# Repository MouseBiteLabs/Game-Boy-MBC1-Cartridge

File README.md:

# Game Boy MBC1 Cartridge

This is my design of a flashable MBC1-based cartridge for the Game Boy. The MBC1 mapper was used in many of the earlier Game Boy games, such as the Super Mario Land series, the Donkey Kong Land series, Metroid II, and one of my personal favorites - the original Link's Awakening. 

This circuit board should cover most, if not all, MBC1 games. The features are as follows:

- Able to make games that use 512 KB (4 Mbit) of ROM and 256 Kbit of RAM, or 2 MB (16 Mbit) of ROM and 64 Kbit of RAM
- Compatibility with all four of the major Game Boy battery management ICs - MM1026, MM1134, BA6129, and BA6735
- The option to add battery backup to the cartridge *without* the need of the original battery management ICs - perfect for MBC1 donors that didn't have batteries in them
- Lower battery consumption compared to some of the original cartridges
- Fully compatible with the <a href="https://www.gbxcart.com/">GBxCart RW</a> so you can transfer games and save files to and from the board

All gerbers and source files can be found in this repo, as this project is fully open source. Technical documentation of the board can be found in the Technical folder.

## Important Things Before You Start

1) To use this board, you need to have an original Game Boy game that uses an MBC1 mapper chip. <a href="https://catskull.net/gb-rom-database/">You can find a list of games and their mappers here</a>. Use the search function. Please note the RAM is in bytes, not bits. Since SRAM in this repo is defined in bits, you need to convert by multiplying the number of bytes by 8.
2) You will need to remove the MBC1 from your donor cartridge for use on this board. This will require a hot air rework station or a hot plate. There's a list below of other parts you can re-use from the donor cartridge.
3) When soldering parts on, it's a good idea to put kapton tape or otherwise cover the bottom cartridge edge. You do not want to get solder on the cartridge contacts.
4) I am not responsible for any damage you do to your self or your property. Attempt this project at your own risk.
5) I do not guarantee design compatibility. You may encounter issues with certain games. There is also a chance I have made an error in the design or the BOM - if this is the case, I will do everything I can to address the problem as quickly as possible.
6) If you are using this board to make games other than for personal use, you must have permission from the originator to use and distribute any ROM images or other related material. You are responsible for making sure you adhere to any license requirements.

DO NOT use my circuit boards for profiting from stolen work - this especially includes homebrew content, ROM hacks, and using fan-made labels without permission from the originator. **Support original creators!**

## Board Characteristics and Order Information

The zipped folder contains all the gerber files for this board. The following options **must** be chosen when ordering boards for yourself.

- Thickness: 0.8mm
- Surface Finish: ENIG
- Gold Fingers: Yes, 30° chamfer

**I sell this blank circuit board on Etsy, so you don't have to buy a bunch of multiples if you don't want to.** (Click the banner!)

You can alternatively use the zipped folder at any board fabricator you like. You may also buy the board from PCBWay using this link (disclosure: I receive 10% of the sale value to go towards future PCB orders of my own):

<a href="https://oshpark.com/shared_projects/bYJcF53Z">The board is also listed on OSH Park as well.</a> **Be sure to get them in 0.8mm thickness if you order from here.**

## Required Equipment

The EEPROMs on the board needs to be programmed somehow. I recommend using the GBxCart, as mentioned. These boards are fully compatible with it, and it makes reflashing games extremely easy using <a href="https://github.com/lesserkuma/FlashGBX">lesserkuma's FlashGBX software</a>.

Alternatively, you can buy an EEPROM programmer with a TSOP adapter. The downside to this method is that you have to desolder the chip every time you want to program it. The <a href="https://flashcatusb.com/">FlashcatUSB</a> is one popular option in retro spaces.

## Battery Safety

When assembling a board, I recommend populating all the parts *except* the battery, and getting it to run initially without it. This is to make it easier to fix any solder connections that might need fixing, without having to worry about getting the battery hot. And if you need to rework anything near the battery after you've put it on the board, be safe and remove it before putting a hot soldering iron next to it.

And this should go without saying, but if you're assembling these boards with a hot plate or hot air, *do not* solder the battery on this way. You should use an iron, and keep heat off of the battery as much as possible. 

(Also check polarity!)

## Board Configurations

The board comes with four sets of jumper pads for solder bridges. SJ1 and SJ2 require you to solder bridge the middle pad either to the top pad or the bottom pad. SJ3 and SJ4 are configured by either leaving them alone or bridging them with solder. Here are the situations where you need to add solder bridges.

### RAM Size Selection (SJ1 and SJ2, or SW1)

These two sets of pads are labelled "RAM SIZE" in the middle of the board. Soldering them will configure the max RAM *and* ROM size. You must configure these pads for every game you make - do not leave them empty (if you have no SRAM, solder to the "64K" setting to maximize ROM space). <a href="https://catskull.net/gb-rom-database/">You can find a list of games here with their respective ROM and RAM sizes.</a>

- Solder bridge SJ1 and SJ2 from their middle pads to the top pads for games that have larger ROM sizes (up to 2 MB, or 16 Mbit of ROM, and up to 64 Kbit of RAM).

- Solder bridge SJ1 and SJ2 from their middle pads to the bottom pads for games that have larger RAM sizes (up to 512 KB, or 4 Mbit of ROM, and up to 256 Kbit of RAM).

- SJ1 and SJ2 must be soldered in the same direction.

- The footprint of these selection pads should allow for a DPDT switch, part number CAS-220A1, to be placed on these pads instead of having to bridge the pads with solder.

### Using an MM1134 or BA6735 for U4 (SJ3)

Bridge the jumper SJ3 if you have either an MM1134 or BA6735 for U4, specifically. Any other battery management IC must leave SJ3 unsoldered.

### Making Games Without RAM (SJ4)

If your game does not have RAM on it (and therefore, you don't need the battery management IC U4), bridge SJ4 with solder. **Do not** bridge SJ4 if you are using U5 (TPS3613) instead of U4.

## Test Points and Final Checkout

On the back of the board are five test points. Here's where they are connected:

- TP1: SRAM supply voltage
- TP2: Battery voltage (after R1)
- TP3: Battery voltage (positive terminal of battery)
- TP4: Ground
- TP5: VCC input voltage

After you assemble your game, you should measure the current out of the battery. But first, you should program it with the GBxCart, or if you programmed the EEPROM separately, put it into a Game Boy and cycle power once. Then, flip the PCB upside down on a non-conductive surface (not your leg), and set your multimeter in DC millivolts (or volts). Put the positive probe on TP3 and the negative probe on TP2. If you used a 10kΩ for R1, as indicated in the BOM, you should read a voltage in the single of millivolts. If you have something much higher, especially voltages above 30mV, then you likely have an issue or short circuit on the board somewhere.

**Note: You need to power up the game at least once before battery currents will make sense - the battery management ICs can start up in an unknown state before applying main power to the board.**

To estimate battery life, see <a href="https://github.com/MouseBiteLabs/Game-Boy-MBC1-Cartridge/tree/main/Technical#estimating-battery-life">this section in the Technical Design Document</a>, or for more in-depth analysis, <a href="https://hackaday.io/project/11864-tritiled/log/72554-determining-maximum-runtime-176-to-202-years-cr2032">this Hackaday post</a>.

### Why not FRAM?

This board is only suitable for using SRAM. One downside to SRAM, if you haven't figured it out yet, is that you need a battery to keep the SRAM powered on even when the game is turned off. So eventually the battery will die, and your save data is lost. Some people have used FRAM, or Ferroelectric RAM, to keep save data around even after the battery dies (specifically, the popular part that's used for FRAM carts is the FM18W08). But, using this FRAM chip has a handful of downsides, and the benefit of keeping save data after the battery dies *in my opinion* does not outweigh the cons, which are as follows:

1) Quality, new stock, 5V tolerant FRAM is expensive ($12+ per part).
2) Cheaper FRAM chips from eBay or Aliexpress are notoriously flaky (anecdotally, ~50% success rate).
3) FRAM memory access requires different chip select timing than SRAM, and the Game Boy expects SRAM, so it is not natively compatible with FRAM carts. The Gameboy Color specifically cannot (easily) be made to properly access FM18W08 chip. You *can* use an OR gate and add the CLK on the cart edge to try to achieve the necessary timing, but it only works (properly) for DMG/MGB/SGB, not the GBC. It usually *works* in practice for GBC, but it's technically a datasheet violation and can potentially cause issues in edge cases. <a href="https://github.com/Gekkio">(Thanks to gekkio for pointing this out!)</a>

Brand new SRAM chips are ~$3, and having the SRAM footprint also allows you to use SRAM from an original cart if desired. You will *easily* get more than a decade of life running on a battery. You're already assembling this cartridge; you can dump the save and replace the battery before then!

Note that this isn't to throw shade at any FRAM-based carts, but for me personally, it's more trouble than it's worth.

## Board Fitment

The shape of this board was originally meant to mimic original Game Boy circuit boards as closely as possible (v1.3 and earlier). Unfortunately, when placed in some aftermarket Game Boy cartridge shells (like those from Cloud Game Store), the circuit board has a lot of freedom to rotate around the main screw hole in the bottom-middle of the cartridge. This can cause misalignment when you put it in a Game Boy, which can cause a game to either not load properly (garbled Game Boy logo) or shut off the Game Boy because of a short circuit. This isn't *dangerous* or anything, just annoying.

In order to make the boards fit nicer in any kind of shell, for v1.4 I added extended tabs of circuit board material to the edges of the cartridges to keep it from rotating too much in shells, which was suggested to me by <a href="https://github.com/orangeglo">orangeglo</a>! (Thanks!)

If you're having trouble fitting the circuit board into a shell, because the tabs interfere with the cart edges, you can safely sand or trim them down as there is no copper within the tabs themselves. The only shell that appears to require any kind of trimming are Kitsch-Bent shells.

## Bill of Materials (BOM)

Your parts list will vary depending on the game you are trying to make, and what chips you have for the battery management (if any). **You cannot use both U4 and U5 - you must choose one or the other.** U4 comes from a donor cartridge, and U5 is a readily available aftermarket option.

Please carefully review the parts you need for the board you are trying to make. Do not add any parts to your build that don't appear in the column for the game you are making. This means you *cannot* populate every component on the board at the same time.

| Reference Designators | Value/Part Number              | Package          | Description        | No save carts | Save carts with MM1134 or BA6735 | Save carts with MM1026 or BA6129 | Save carts without donor U4 chip | Source                                           |
| --------------------- | ------------------------------ | ---------------- | ------------------ | ------------- | -------------------------------- | -------------------------------- | -------------------------------- | ------------------------------------------------ |
| B1                    | CR2032, CR2025, CR2016         | CR2032           | Backup Battery     |               | x                                | x                                | x                                | [https://mou.sr/3SeAzfT](https://mou.sr/3SeAzfT) |
| C1                    | 0.1uF                          | 0603             | Capacitor (MLCC)   | x             | x                                | x                                | x                                | [https://mou.sr/3ENc15O](https://mou.sr/3ENc15O) |
| C4                    | 0.1uF                          | 0603             | Capacitor (MLCC)   |               | x                                | x                                |                                  | [https://mou.sr/3ENc15O](https://mou.sr/3ENc15O) |
| C5                    | 0.1uF                          | 0603             | Capacitor (MLCC)   |               | x                                | x                                | x                                | [https://mou.sr/3ENc15O](https://mou.sr/3ENc15O) |
| C6                    | 10uF                           | 0603             | Capacitor (MLCC)   |               | x                                | x                                | x                                | [https://mou.sr/3mZtSkF](https://mou.sr/3mZtSkF) |
| C7                    | 0.1uF                          | 0603             | Capacitor (MLCC)   | x             | x                                | x                                | x                                | [https://mou.sr/3ENc15O](https://mou.sr/3ENc15O) |
| C8                    | 0.1uF                          | 0603             | Capacitor (MLCC)   |               |                                  |                                  | x                                | [https://mou.sr/3ENc15O](https://mou.sr/3ENc15O) |
| Q1                    | 2N7002                         | SOT-23           | N-Channel FET      |               |                                  |                                  | x                                | [https://mou.sr/3rgfh6J](https://mou.sr/3rgfh6J) |
| Q2                    | 2N7002                         | SOT-23           | N-Channel FET      |               |                                  | x                                |                                  | [https://mou.sr/3rgfh6J](https://mou.sr/3rgfh6J) |
| R1                    | 10k                            | 0603             | Resistor           |               | x                                | x                                | x                                | [https://mou.sr/3riR7IH](https://mou.sr/3riR7IH) |
| R3                    | 49.9k                          | 0603             | Resistor           |               | x                                | x                                | x                                | https://mou.sr/3Q3NRZO                           |
| R4                    | 49.9k                          | 0603             | Resistor           |               | x                                | x                                | x                                | https://mou.sr/3Q3NRZO                           |
| R5                    | 49.9k                          | 0603             | Resistor           | x             | x                                | x                                | x                                | https://mou.sr/3Q3NRZO                           |
| R6                    | 49.9k                          | 0603             | Resistor           | x             | x                                | x                                | x                                | https://mou.sr/3Q3NRZO                           |
| R7                    | 10k                            | 0603             | Resistor           |               |                                  | x                                |                                  | [https://mou.sr/3riR7IH](https://mou.sr/3riR7IH) |
| R8                    | 10k                            | 0603             | Resistor           | x             | x                                | x                                | x                                | [https://mou.sr/3riR7IH](https://mou.sr/3riR7IH) |
| R9                    | 130k                           | 0603             | Resistor           |               |                                  |                                  | x                                | https://mou.sr/3MjXliy                           |
| R10                   | 49.9k                          | 0603             | Resistor           |               |                                  |                                  | x                                | https://mou.sr/3Q3NRZO                           |
| U1                    | 29F016, 29F032, 29F033         | TSOP-48, TSOP-40 | Flash EEPROM       | x             | x                                | x                                | x                                | AliExpress or eBay                               |
| U2                    | MBC1                           | SOP-24           | MBC1 Mapper        | x             | x                                | x                                | x                                | Donor MBC1 Game Boy cartridge                    |
| U3                    | AS6C6264, AS6C62256            | SOP-28           | SRAM               |               | x                                | x                                | x                                | [https://mou.sr/450klcY](https://mou.sr/450klcY) |
| U4                    | MM1026, MM1134, BA6129, BA6735 | SOIC-8           | Battery Management |               | x                                | x                                |                                  | Donor Game Boy cartridge                         |
| U5                    | TPS3613                        | MSOP-10          | Battery Management |               |                                  |                                  | x                                | https://mou.sr/45Ir2kh                           |

*Note that C9 - C11 footprints are only included on the board for strange edge cases that may require them sometime in the future; do not populate! See the technical design document for more information.*

### Usable Donor Cartridge Parts

You can use a few parts from the donor cart on the new board to save some money. Note that you will generally get better reliability with new parts as opposed to old ones. For example: I have seen failed RAM chips from donors in the past.

1) **U2: MBC1** - This one is required
2) **U3: SRAM** - You can use this part *only if* the game you're making uses the same or less amount of RAM that the donor cartridge does
3) **U4: Battery Management IC** - Using this is probably preferred over the TPS3613 because it'll save you money and parts to put on

You could probably transfer over most of the 0.1uF capacitors but they're pretty cheap anyway, so I generally just recommend buying new resistors and capacitors.

### Capacitors C9 to C11

If you want to experiment with the capacitors C9 to C11, see this info below. **Be aware that adding these components in some of my tests actually ***stopped*** games from working, so again, assume that if you have a problem it lies elsewhere first, because it almost certainly does.**
- C9 is a capacitor connected nearby the MBC1's /WR pin to GND. These were populated on some cartridges, and have a value of approximately 1 nF (0.001 uF).
- C10 is a capacitor connected nearby the MBC1's /RESET pin to GND. A spot for this capacitor was included on some MBC1 carts, but I cannot locate an instance of it actually being used when looking through the gbhwdb. I don't actually know what value this capacitor would need to be, so I am guessing 1 nF.
- C11 is a capacitor that I have added that was not used on any original Game Boy board. It connects to the SRAM's /CE pin, bypassing to GND. I have added this in the event incompatibilities arise with newer SRAM chips that have much faster speeds than older SRAM chips. This was a problem I encountered on some of my NES cartridges, so this is here just in case, but I have not found an instance where it's required.

## Things to Remember

- The footprint for the EEPROM is specifically for 29F016 - it has 48 pins. However, 29F032 and 29F033 are only 40 pin devices. They still work fine on the board though - place them in the center of the footprint, and leave the outer two pins on each corner empty
- The 29F016, 29F032, and 29F033 have been known to occasionally be defective upon arrival. They're either used, or new old stock, and usually only available from AliExpress.
- The footprint for the battery can fit a CR2032, CR2025, or CR2016 with solder tabs. The only difference is the mAh capacity (larger number = longer life). If you get Panasonic tabbed batteries, you may have to trim the battery tabs to make them fit on the footprint.
  - For untabbed coin cells, you can find battery retainer adapters online, <a href="https://retrogamerepairshop.com/products/hdr-game-boy-game-battery-retainer?variant=40511013290156">like this one,</a> but only for board revision v1.4. It will not fit on earlier revisions.
- For battery management, use either U4 *or* U5 and supporting components. **Do not** use U4 and U5 simultaneously on one board. They will interfere with each other.
- Generally, ROM sizes are conveyed in terms of kilo**bytes** and mega**bytes** (KB, MB). RAM size is usually conveyed in terms of kilo**bits** or mega**bits** (Kbit, Mbit). You can convert Kbit and Mbit to KB and MB by dividing Kbit or Mbit by 8. For example, 256 Kbit = 32 KB.
- You only need to provide ROM and RAM chips that have at least *or greater* the size of the game you are trying to make. That means you can use a 256 Kbit SRAM chip for a game that only requires 64 Kbit of RAM!

## Labels

If you want a Bucket Mouse branded label for your cartridge, look no further than <a href="https://krizdingus.com/mousebitelabs/">krizdingus's designs</a>. Special thanks to Kris for designing these, they look awesome! (If you are going to order/print these, use the high-res images hosted on his website, and *keep the labels for personal or non-commercial use only.*)

## Revision History

### v1.4
- Reduced cart edge by 0.1 mm for better fitment
- Adjusted battery placement to support more battery holders
- Added tabs on the board edges to allow the circuit board to fit better in aftermarket cartridge shells

### v1.3
- Extended cart edge down by 0.25 mm for better fitment
- Added OSHW logo and "SUPPORT ORIGINAL CREATORS!"

### v1.2
- Replaced non-donor battery management circuitry with a TPS3613-based circuit for smaller BOM and easier routing

### v1.1
- Moved all parts on the top down to allow for compatibility with DMG-style shells
- Rotated battery for more space
- Widen SRAM footprint for easier soldering
- Renamed some reference designators for consistency between designs
- Changed silkscreen for clarity

### v1.0
- Prototype revision

## Resources and Acknowledgements

- <a href="http://www.devrs.com/gb/files/hardware.html">Jeff Frohwein's GameBoy Tech Page</a>
- <a href="https://gbhwdb.gekkio.fi/">Game Boy Hardware Database</a>
- <a href="https://catskull.net/gb-rom-database/">Nintendo Gameboy Game List</a>
- <a href="https://wiki.tauwasser.eu/view/MBC1">Tauwasser's Wiki</a>
- <a href="https://www.gbxcart.com/">insideGadgets discord server for GBxCart RW compatibility requirements</a>
- <a href="https://github.com/lesserkuma/FlashGBX">Lesserkuma's FlashGBX software</a>
- <a href="https://www.alldatasheet.com/datasheet-pdf/pdf/99104/MITSUBISHI/MM1026.html">System Reset IC Datasheet</a>
- <a href="https://www.ti.com/lit/ds/symlink/tps3613-01.pdf?HQS=dis-mous-null-mousermode-dsf-pf-null-wwe&ts=1698238885366&ref_url=https%253A%252F%252Feu.mouser.com%252F">TPS3613 Datasheet</a>
- Board outline modified from <a href="https://tinkerer.us/projects/homebrew-gameboy-cartridge.html">Dillon Nichols's Homebrew Gameboy Cartridge project</a>
- Thanks to <a href="https://github.com/orangeglo">orangeglo</a> for his suggestion of adding spacers around the board edge for better fitment in aftermarket cartridges
- Some components from <a href="https://github.com/adafruit/Adafruit-Eagle-Library">Adafruit's Eagle parts library</a>
- Some components from <a href="https://www.snapeda.com/">SnapMagic</a>
- Thank you to <a href="https://github.com/Gekkio">gekkio</a> for their deep Game Boy knowledge resources, and for collaboration in demystifying some of the design choices on Game Boy cartridges
- Thanks to the awesome members of the <a href="https://moddedgameboy.club/">Modded Gameboy Club</a> for their feedback and support during the entire project development

## License

<br />This work is licensed under a <a rel="license" href="http://creativecommons.org/licenses/by-sa/4.0/">Creative Commons Attribution-ShareAlike 4.0 International License</a>. You are able to copy and redistribute the material in any medium or format, as well as remix, transform, or build upon the material for any purpose (even commercial) - but you **must** give appropriate credit, provide a link to the license, and indicate if any changes were made.

©MouseBiteLabs 2023

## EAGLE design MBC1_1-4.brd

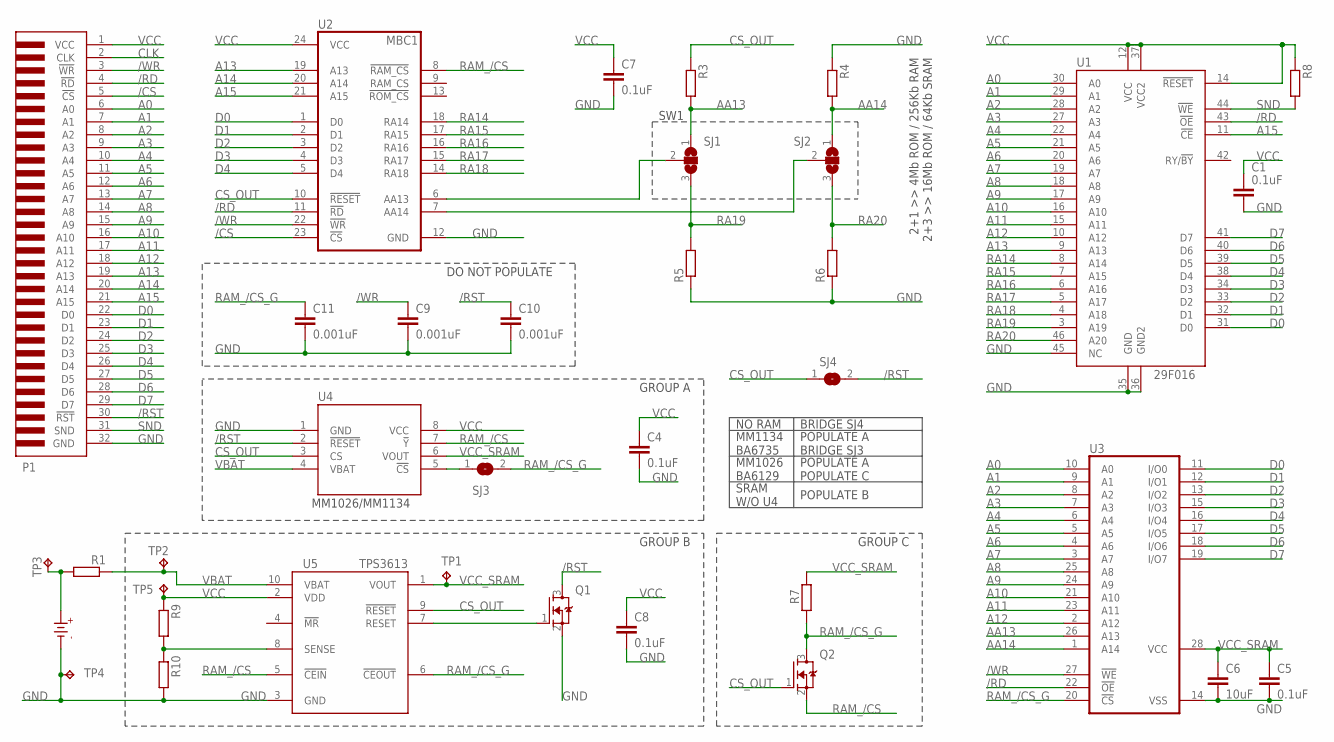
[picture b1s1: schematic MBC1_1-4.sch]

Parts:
B1: CR2025
C1, C4, C5, C7, C8: 0.1uF; C0603
C6: 10uF; C0603
C9, C10, C11: 0.001uF; C0603
P1: GBC_CARTTAB; GBC_CART_TABBED
Q1, Q2: 2N7002; SOT23
R1, R3, R4, R5, R6, R7, R8, R9, R10: RR0603; R0603
SJ1, SJ2: SJ2W; SJ_2
SJ3, SJ4: SJ
TP1, TP2, TP3, TP4, TP5: TPB1,27; B1,27
U1: 29F016; TSOP-48
U2: MBC1; SOP-24
U3: 62256_SRAM; SOP-28L
U4: MM1134; SOIC-8
U5: TPS3613; MSOP-10

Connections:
/CS: P1.5 (!CS), U2.23 (!CS)
/RD: P1.4 (!RD), U1.43 (!OE), U2.11 (!RD), U3.22 (!OE)
/RST: C10.1, P1.30 (!RST), Q1.3 (D), SJ4.2, U4.2 (!RESET)
/WR: C9.1, P1.3 (!WR), U2.22 (!WR), U3.27 (!WE)
A0: P1.6 (A0), U1.30 (A0), U3.10 (A0)
A1: P1.7 (A1), U1.29 (A1), U3.9 (A1)
A2: P1.8 (A2), U1.28 (A2), U3.8 (A2)
A3: P1.9 (A3), U1.27 (A3), U3.7 (A3)
A4: P1.10 (A4), U1.22 (A4), U3.6 (A4)
A5: P1.11 (A5), U1.21 (A5), U3.5 (A5)
A6: P1.12 (A6), U1.20 (A6), U3.4 (A6)
A7: P1.13 (A7), U1.19 (A7), U3.3 (A7)
A8: P1.14 (A8), U1.18 (A8), U3.25 (A8)
A9: P1.15 (A9), U1.17 (A9), U3.24 (A9)
A10: P1.16 (A10), U1.16 (A10), U3.21 (A10)
A11: P1.17 (A11), U1.15 (A11), U3.23 (A11)
A12: P1.18 (A12), U1.10 (A12), U3.2 (A12)
A13: P1.19 (A13), U1.9 (A13), U2.19 (A13)
A14: P1.20 (A14), U2.20 (A14)
A15: P1.21 (A15), U1.11 (!CE), U2.21 (A15)
AA13: R3.2, SJ1.1, U3.26 (A13)
AA14: R4.2, SJ2.1, U3.1 (A14)
CLK: P1.2 (CLK)
CS_OUT: Q2.1 (G), R3.1, SJ4.1, U2.10 (!RESET), U4.3 (CS), U5.9 (!RESET)
D0: P1.22 (D0), U1.31 (D0), U2.1 (D0), U3.11 (I/O0)
D1: P1.23 (D1), U1.32 (D1), U2.2 (D1), U3.12 (I/O1)
D2: P1.24 (D2), U1.33 (D2), U2.3 (D2), U3.13 (I/O2)
D3: P1.25 (D3), U1.34 (D3), U2.4 (D3), U3.15 (I/O3)
D4: P1.26 (D4), U1.38 (D4), U2.5 (D4), U3.16 (I/O4)
D5: P1.27 (D5), U1.39 (D5), U3.17 (I/O5)
D6: P1.28 (D6), U1.40 (D6), U3.18 (I/O6)
D7: P1.29 (D7), U1.41 (D7), U3.19 (I/O7)
GND: B1.-, C1.2, C4.2, C5.2, C6.2, C7.2, C8.2, C9.2, C10.2, C11.2, P1.32 (GND), Q1.2 (S), R4.1, R5.1, R6.1, R10.2, TP4.TP, U1.35 (GND), U1.36 (GND2), U1.45 (NC), U2.12 (GND), U3.14 (VSS), U4.1 (GND), U5.3 (GND)
unnamed: SJ2.2, U2.7 (AA14)
unnamed: SJ1.2, U2.6 (AA13)
unnamed: B1.+, R1.2, TP3.TP
unnamed: SJ3.1, U4.5 (!CS)
unnamed: Q1.1 (G), U5.7 (RESET)
unnamed: R9.2, R10.1, U5.8 (SENSE)
RA14: U1.8 (A14), U2.18 (RA14)
RA15: U1.7 (A15), U2.17 (RA15)
RA16: U1.6 (A16), U2.16 (RA16)
RA17: U1.5 (A17), U2.15 (RA17)
RA18: U1.4 (A18), U2.14 (RA18)
RA19: R5.2, SJ1.3, U1.3 (A19)
RA20: R6.2, SJ2.3, U1.46 (A20)
RAM_/CS: Q2.2 (S), U2.8 (!RAM_CS), U4.7 (!Y), U5.5 (!CEIN)
RAM_/CS_G: C11.1, Q2.3 (D), R7.1, SJ3.2, U3.20 (!CS), U5.6 (!CEOUT)
SND: P1.31 (SND), R8.2, U1.44 (!WE)
VBAT: R1.1, TP2.TP, U4.4 (VBAT), U5.10 (VBAT)
VCC: C1.1, C4.1, C7.1, C8.1, P1.1 (VCC), R8.1, R9.1, TP5.TP, U1.12 (VCC), U1.14 (!RESET), U1.37 (VCC2), U2.24 (VCC), U4.8 (VCC), U5.2 (VDD)
VCC_SRAM: C5.1, C6.1, R7.2, TP1.TP, U3.28 (VCC), U4.6 (VOUT), U5.1 (VOUT)

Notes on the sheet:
2+1 >> 4Mb ROM / 256Kb RAM 2+3 >> 16Mb ROM / 64Kb SRAM
GROUP A
GROUP C
NO RAM
BRIDGE SJ4
MM1134 BA6735
POPULATE A BRIDGE SJ3
MM1026 BA6129
POPULATE A POPULATE C
SRAM W/O U4
POPULATE B
MM1026/MM1134
GROUP B
DO NOT POPULATE
SW1

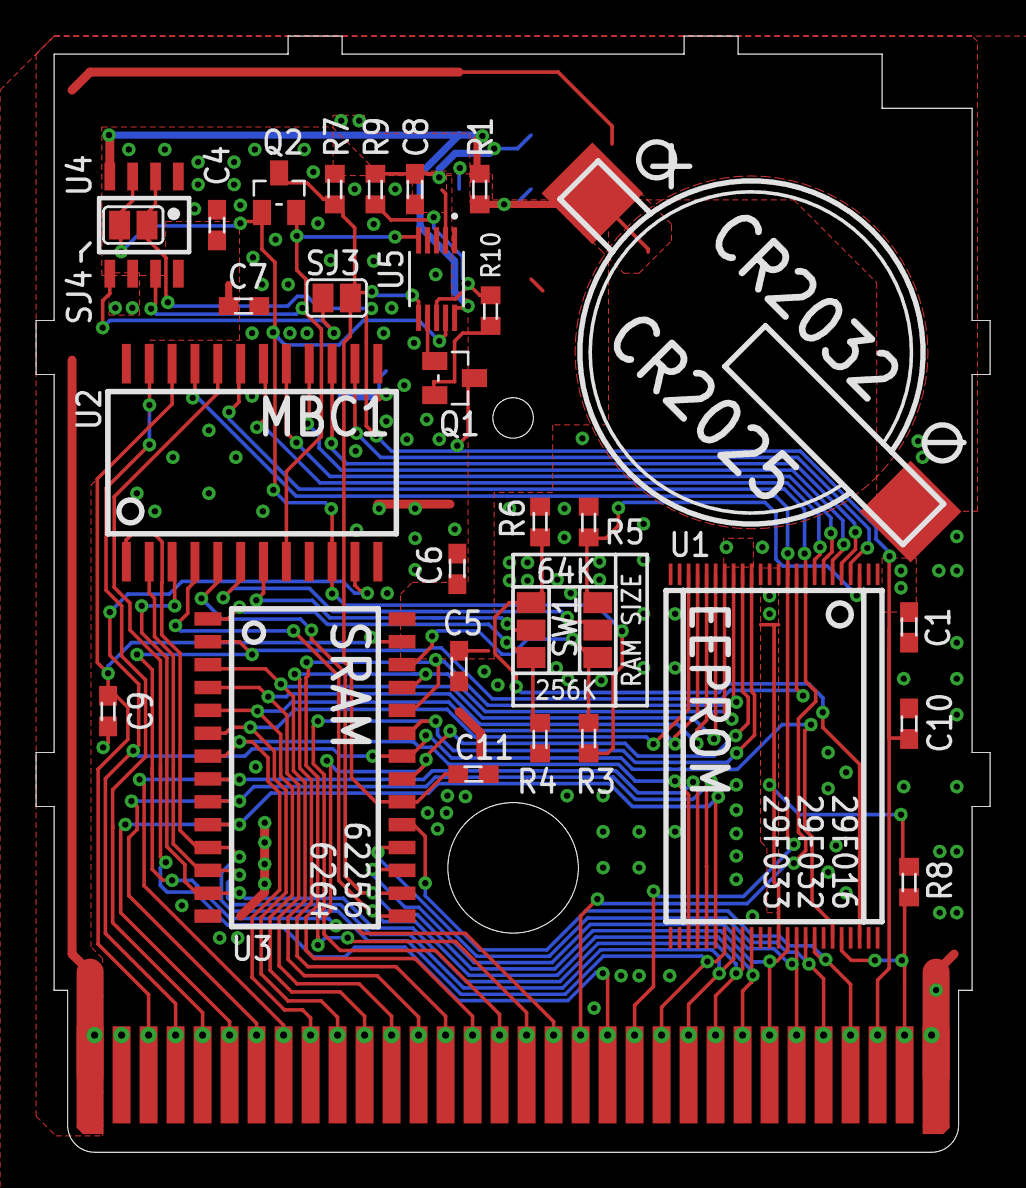
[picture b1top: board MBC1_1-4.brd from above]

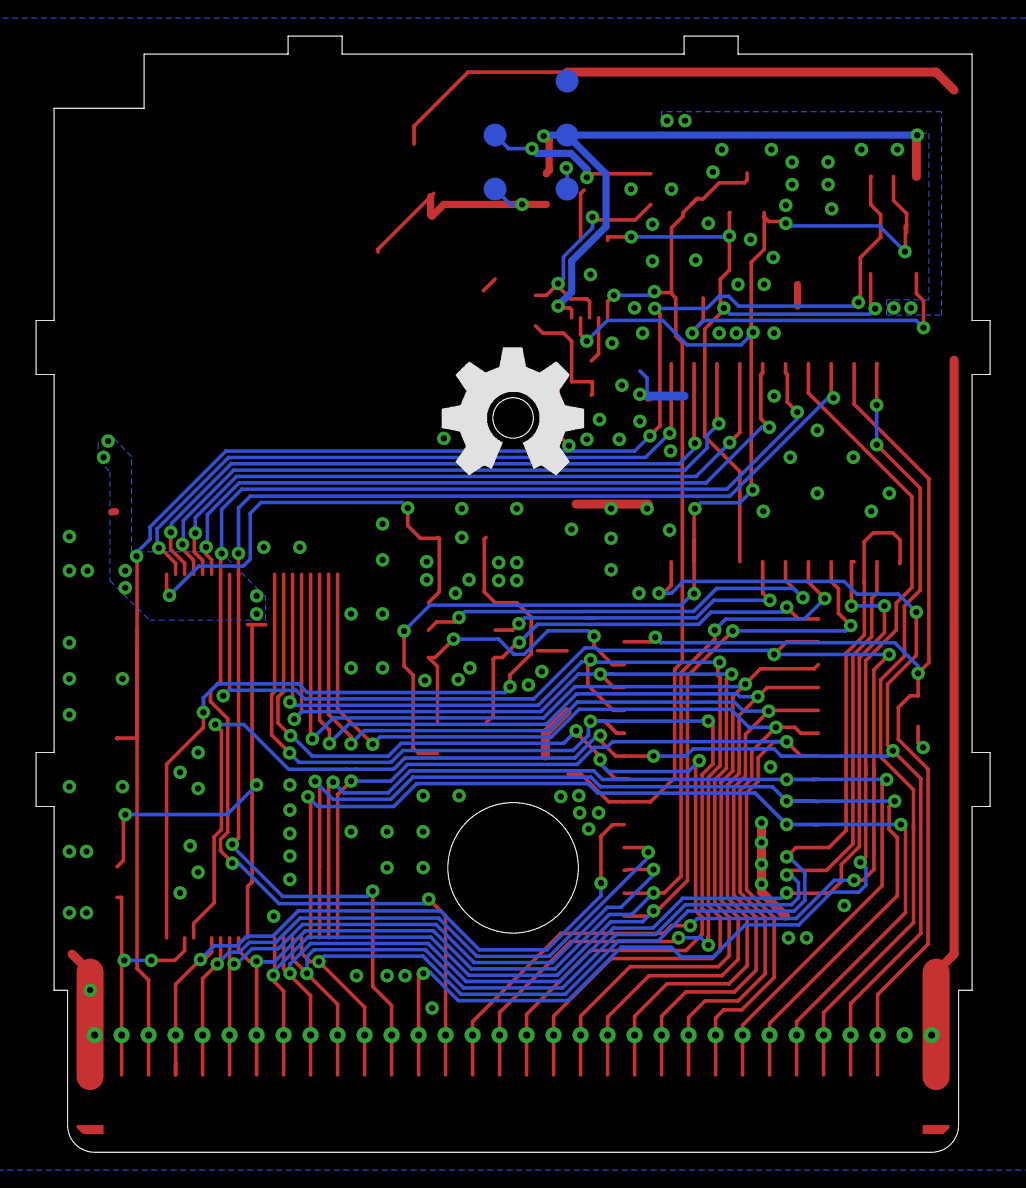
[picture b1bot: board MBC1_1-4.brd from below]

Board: 2 copper layers, 53.0 x 62.0 mm, 36 parts (5 on the bottom side), 51 nets.

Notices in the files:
README.md:
This work is licensed under a Creative Commons Attribution-ShareAlike 4.0 International License. You are able to copy and redistribute the material in any medium or format, as well as remix, transform, or build upon the material for any purpose (even commercial) - but you **must** give appropriate credit, provide a link t
©MouseBiteLabs 2023
